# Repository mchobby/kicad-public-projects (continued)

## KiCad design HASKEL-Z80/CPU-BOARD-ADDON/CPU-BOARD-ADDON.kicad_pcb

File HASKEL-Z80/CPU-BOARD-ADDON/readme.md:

# CPU-BOARD-ADDON aka RCIO

The CPU-BOARD have been designed to deal with analogic phone system (via analog-board and interface-board).<br />In its initial state, the CPU-BOARD does not have HMI (Human Machine Interface) to allow the user to deal with the CPU-BOARD.

-1.0.jpg)

The aim of the CPU-BOARD-ADDON is to overcome this limitation with the following features:
* The CPU-BOARD-ADDON is inserted between the Z80 CPU and the CPU-BOARD, so we have access to all the buses and all the CPU signals
* **Append 8 bits outputs** (LEDs) directly controled by a IO port.<br />Requires only 2 instructions `ld a, 0xFF` followed by `out (0x1D),a`
* **Append 8 bits inputs** (button) directly accessible on IO port.<br />Requires only 2 instructions `in a,(0x1C)` followed by `ld d,a`.
* **RC2014 compatible bus** exposing all the CPU signals.<br />The RC2014 bus will be used to append additional expansion boards like [SIO-ADDON](../SIO-ADDON), [I2C-ADDON](../I2C-ADDON), etc.

The additional Input/Ouput will be very handy as basic HMI interface for testing the initial ASSEMBLY on the CPU-BOARD.

Notice: The "RCIO" comes from contraction of **RC**2014 bus and additional **I/O** .

The CPU-BOARD-ADDON will take place as follow on the CPU-BOARD.

# Schematic

Schematic is also available as PDF:
* [CPU-BOARD-ADDON-1.0.pdf](docs/CPU-BOARD-ADDON-1.0.pdf) pdf
* [CPU-BOARD-ADDON-1.1.pdf](docs/CPU-BOARD-ADDON-1.1.pdf) pdf

# Testing code

They are available on the [Z80-ASM/](../Z80-ASM) folder

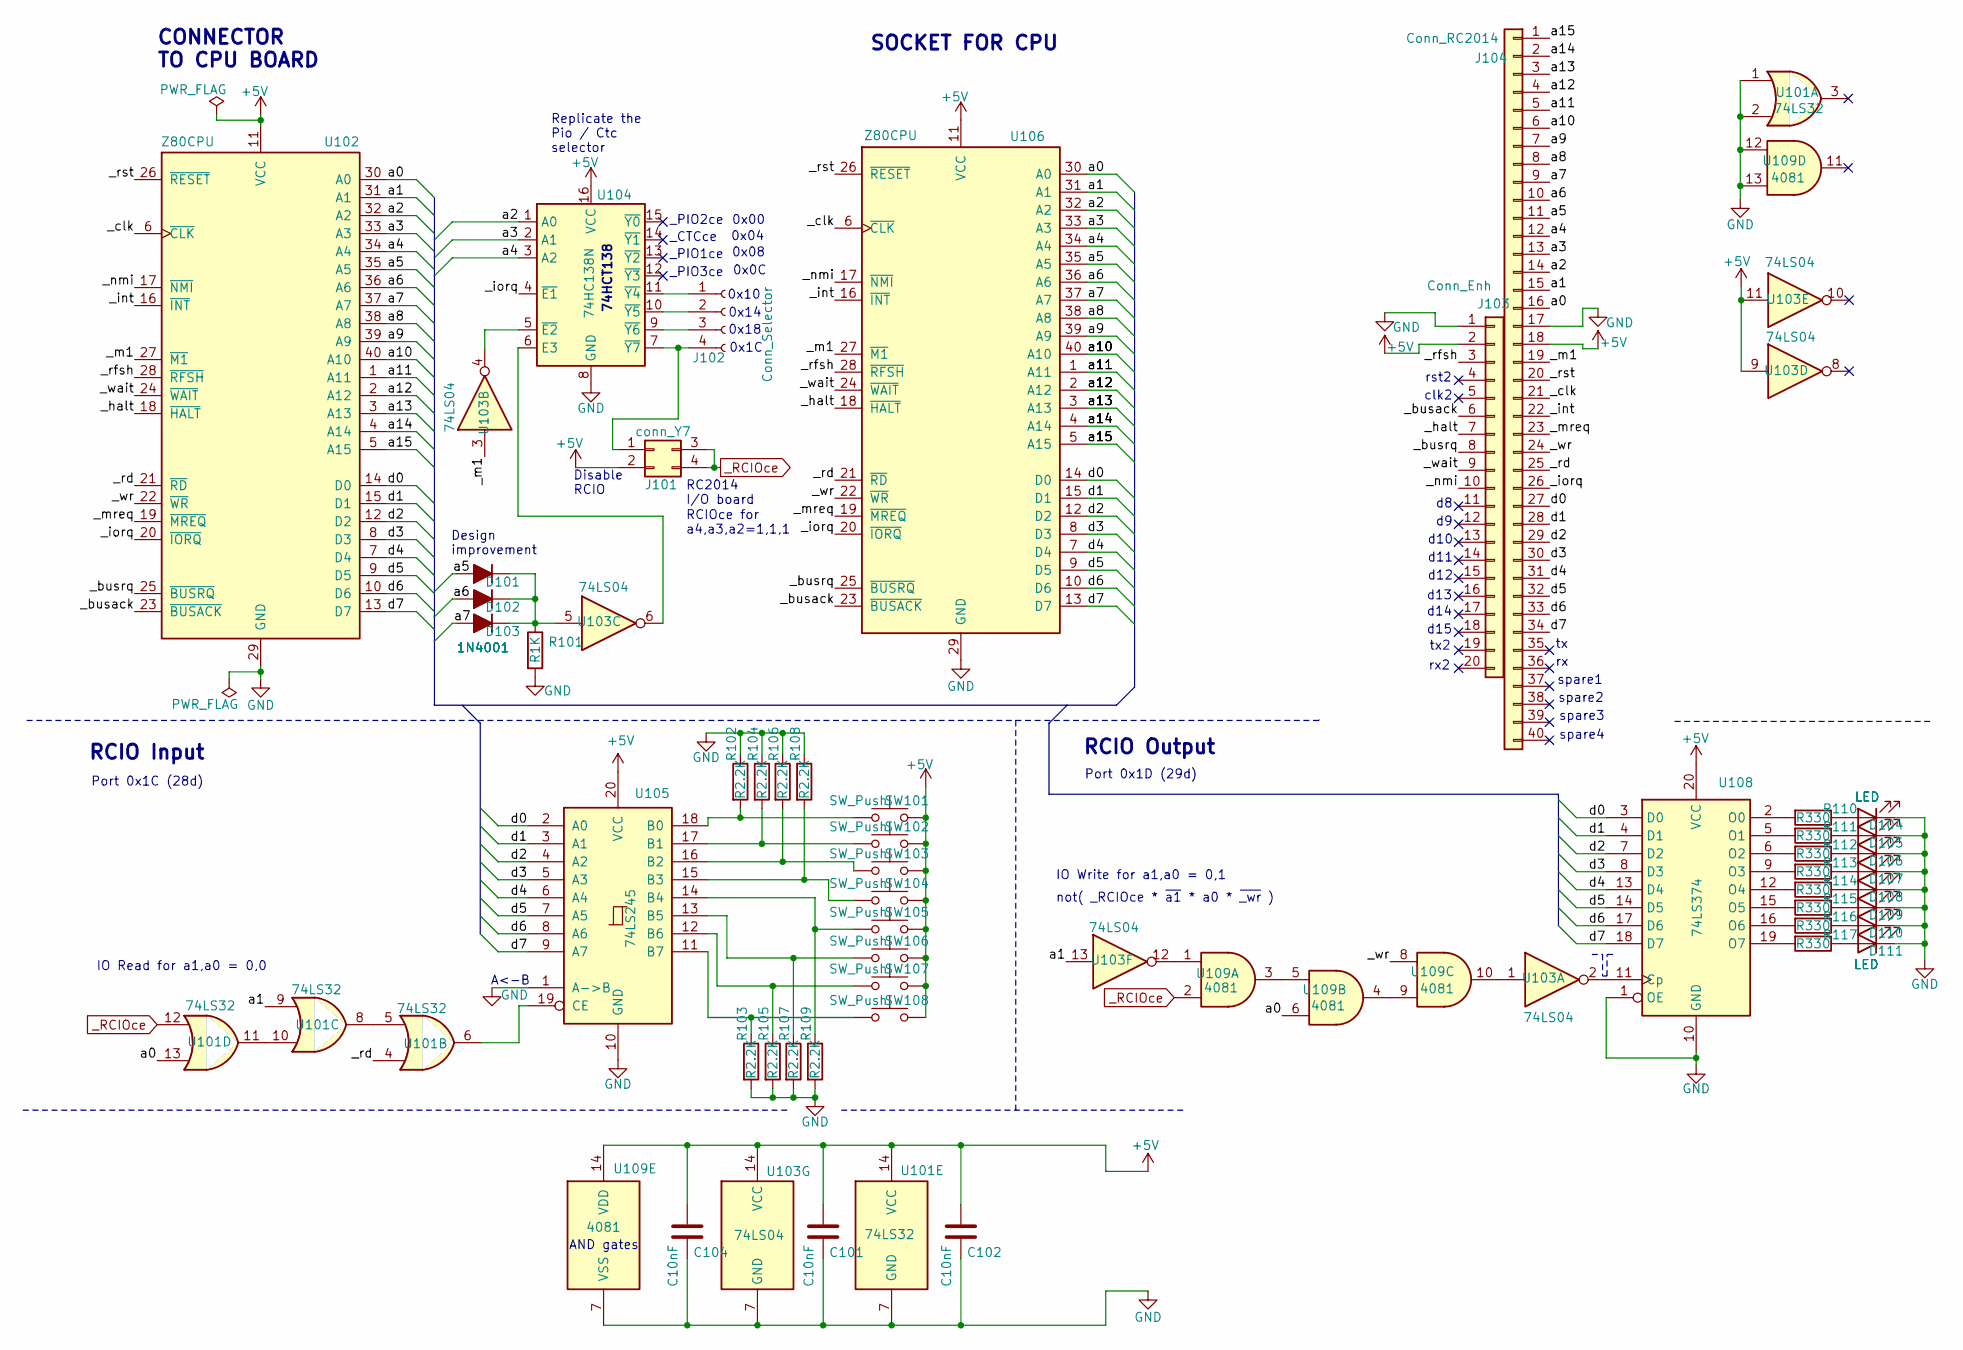
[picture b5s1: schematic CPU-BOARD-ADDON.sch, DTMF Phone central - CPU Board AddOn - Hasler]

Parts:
C101, C102, C104: C10nF; C_Disc_D3.4mm_W2.1mm_P2.50mm
D101, D102, D103: 1N4001; D_A-405_P10.16mm_Horizontal
D104, D105, D106, D107, D108, D109, D110, D111: LED; LED_D3.0mm_FlatTop
J101: conn_Y7; PinHeader_2x02_P2.54mm_Vertical
J102: Conn_Selector; PinHeader_1x04_P2.54mm_Vertical
J103: Conn_Enh; PinHeader_1x20_P2.54mm_Vertical
J104: Conn_RC2014; PinHeader_1x40_P2.54mm_Vertical
R101: R1K; R_1206_3216Metric_Pad1.30x1.75mm_HandSolder
R102, R103, R104, R105, R106, R107, R108, R109: R2.2K; R_1206_3216Metric_Pad1.30x1.75mm_HandSolder
R110, R111, R112, R113, R114, R115, R116, R117: R330; R_1206_3216Metric_Pad1.30x1.75mm_HandSolder
SW101, SW102, SW103, SW104, SW105, SW106, SW107, SW108: SW_Push; SW_Push_TL3305G_NO_4.5x4.5mm_H4.5mm
U101: 74LS32; DIP-14_W7.62mm_Socket
U102, U106: Z80CPU; DIP-40_W15.24mm_Socket_LongPads
U103: 74LS04; DIP-14_W7.62mm_Socket
U104: 74HC138N; DIP-16_W7.62mm_Socket
U105: 74LS245; DIP-20_W7.62mm_Socket
U108: 74LS374; DIP-20_W7.62mm_Socket
U109: 4081; DIP-14_W7.62mm_Socket

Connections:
+5V: C101.1, C102.1, C104.1, J101.2, J103.2, J104.18, SW101.2, SW102.2, SW103.2, SW104.2, SW105.2, SW106.2, SW107.2, SW108.2, U101.14 (VCC), U102.11 (VCC), U103.9, U103.11, U103.14 (VCC), U104.16 (VCC), U105.20 (VCC), U106.11 (VCC), U108.20 (VCC), U109.14 (VDD); also elsewhere on the board
/_busack: J103.6, U102.23 (~BUSACK~), U106.23 (~BUSACK~)
/_busrq: J103.8, U102.25 (~BUSRQ~), U106.25 (~BUSRQ~)
/_clk: J104.21, U102.6 (~CLK~), U106.6 (~CLK~)
/_halt: J103.7, U102.18 (~HALT~), U106.18 (~HALT~)
/_int: J104.22, U102.16 (~INT~), U106.16 (~INT~)
/_iorq: J104.26, U102.20 (~IORQ~), U104.4 (~E1), U106.20 (~IORQ~)
/_m1: J104.19, U102.27 (~M1~), U103.3, U106.27 (~M1~)
/_mreq: J104.23, U102.19 (~MREQ~), U106.19 (~MREQ~)
/_nmi: J103.10, U102.17 (~NMI~), U106.17 (~NMI~)
/_rd: J104.25, U101.4, U102.21 (~RD~), U106.21 (~RD~)
/_rfsh: J103.3, U102.28 (~RFSH~), U106.28 (~RFSH~)
/_rst: J104.20, U102.26 (~RESET~), U106.26 (~RESET~)
/_wait: J103.9, U102.24 (~WAIT~), U106.24 (~WAIT~)
/_wr: J104.24, U102.22 (~WR~), U106.22 (~WR~), U109.8
/a0: J104.16, U101.13, U102.30 (A0), U106.30 (A0), U109.6
/a1: J104.15, U101.9, U102.31 (A1), U103.13, U106.31 (A1)
/a2: J104.14, U102.32 (A2), U104.1 (A0), U106.32 (A2)
/a3: J104.13, U102.33 (A3), U104.2 (A1), U106.33 (A3)
/a4: J104.12, U102.34 (A4), U104.3 (A2), U106.34 (A4)
/a5: D101.2 (A), J104.11, U102.35 (A5), U106.35 (A5)
/a6: D102.2 (A), J104.10, U102.36 (A6), U106.36 (A6)
/a7: D103.2 (A), J104.9, U102.37 (A7), U106.37 (A7)
/a8: J104.8, U102.38 (A8), U106.38 (A8)
/a9: J104.7, U102.39 (A9), U106.39 (A9)
/a10: J104.6, U102.40 (A10), U106.40 (A10)
/a11: J104.5, U102.1 (A11), U106.1 (A11)
/a12: J104.4, U102.2 (A12), U106.2 (A12)
/a13: J104.3, U102.3 (A13), U106.3 (A13)
/a14: J104.2, U102.4 (A14), U106.4 (A14)
/a15: J104.1, U102.5 (A15), U106.5 (A15)
/d0: J104.27, U102.14 (D0), U105.2 (A0), U106.14 (D0), U108.3 (D0)
/d1: J104.28, U102.15 (D1), U105.3 (A1), U106.15 (D1), U108.4 (D1)
/d2: J104.29, U102.12 (D2), U105.4 (A2), U106.12 (D2), U108.7 (D2)
/d3: J104.30, U102.8 (D3), U105.5 (A3), U106.8 (D3), U108.8 (D3)
/d4: J104.31, U102.7 (D4), U105.6 (A4), U106.7 (D4), U108.13 (D4)
/d5: J104.32, U102.9 (D5), U105.7 (A5), U106.9 (D5), U108.14 (D5)
/d6: J104.33, U102.10 (D6), U105.8 (A6), U106.10 (D6), U108.17 (D6)
/d7: J104.34, U102.13 (D7), U105.9 (A7), U106.13 (D7), U108.18 (D7)
GND: C101.2, C102.2, C104.2, D104.1 (K), D105.1 (K), D106.1 (K), D107.1 (K), D108.1 (K), D109.1 (K), D110.1 (K), D111.1 (K), J103.1, J104.17, R101.2, R102.1, R103.2, R104.1, R105.2, R106.1, R107.2, R108.1, R109.2, U101.1, U101.2, U101.7 (GND), U102.29 (GND), U103.7 (GND), U104.8 (GND), U105.1 (A->B), U105.10 (GND), U106.29 (GND), U108.1 (OE), U108.10 (GND), U109.7 (VSS), U109.12, U109.13; also elsewhere on the board
unnamed: D101.1 (K), D102.1 (K), D103.1 (K), R101.1, U103.5
unnamed: D104.2 (A), R110.1
unnamed: D105.2 (A), R111.1
unnamed: D106.2 (A), R112.1
unnamed: D107.2 (A), R113.1
unnamed: D108.2 (A), R114.1
unnamed: D109.2 (A), R115.1
unnamed: D110.2 (A), R116.1
unnamed: D111.2 (A), R117.1
unnamed: J101.1, J102.4, U104.7 (~Y7)
unnamed: J102.1, U104.11 (~Y4)
unnamed: J102.2, U104.10 (~Y5)
unnamed: J102.3, U104.9 (~Y6)
unnamed: R102.2, SW101.1, U105.18 (B0)
unnamed: R103.1, SW108.1, U105.11 (B7)
unnamed: R104.2, SW102.1, U105.17 (B1)
unnamed: R105.1, SW107.1, U105.12 (B6)
unnamed: R106.2, SW103.1, U105.16 (B2)
unnamed: R107.1, SW106.1, U105.13 (B5)
unnamed: R108.2, SW104.1, U105.15 (B3)
unnamed: R109.1, SW105.1, U105.14 (B4)
unnamed: R110.2, U108.2 (O0)
unnamed: R111.2, U108.5 (O1)
unnamed: R112.2, U108.6 (O2)
unnamed: R113.2, U108.9 (O3)
unnamed: R114.2, U108.12 (O4)
unnamed: R115.2, U108.15 (O5)
unnamed: R116.2, U108.16 (O6)
unnamed: R117.2, U108.19 (O7)
unnamed: U101.5, U101.8
unnamed: U101.6, U105.19 (CE)
unnamed: U101.10, U101.11
unnamed: U103.1, U109.10
unnamed: U103.2, U108.11 (Cp)
unnamed: U103.4, U104.5 (~E2)
unnamed: U103.6, U104.6 (E3)
unnamed: U103.12, U109.1
unnamed: U109.3, U109.5
unnamed: U109.4, U109.9
_RCIOce: J101.3, J101.4, U101.12, U109.2

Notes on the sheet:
CONNECTOR TO CPU BOARD
SOCKET FOR CPU
_PIO2ce
_CTCce
_PIO1ce
_PIO3ce
RC2014 I/O board
Replicate the Pio / Ctc selector
A<-B
IO Read for a1,a0 = 0,0
RCIOce for a4,a3,a2=1,1,1
RCIO Input
Port 0x1C (28d)
RCIO Output
Port 0x1D (29d)
Disable RCIO
IO Write for a1,a0 = 0,1
Design improvement
d10
d11
d12
d13
d14
d15
tx2
rx2
spare1
spare2
spare3
spare4
rst2
clk2
0x00
0x04
0x08
0x0C
0x10
0x14
0x18
0x1C

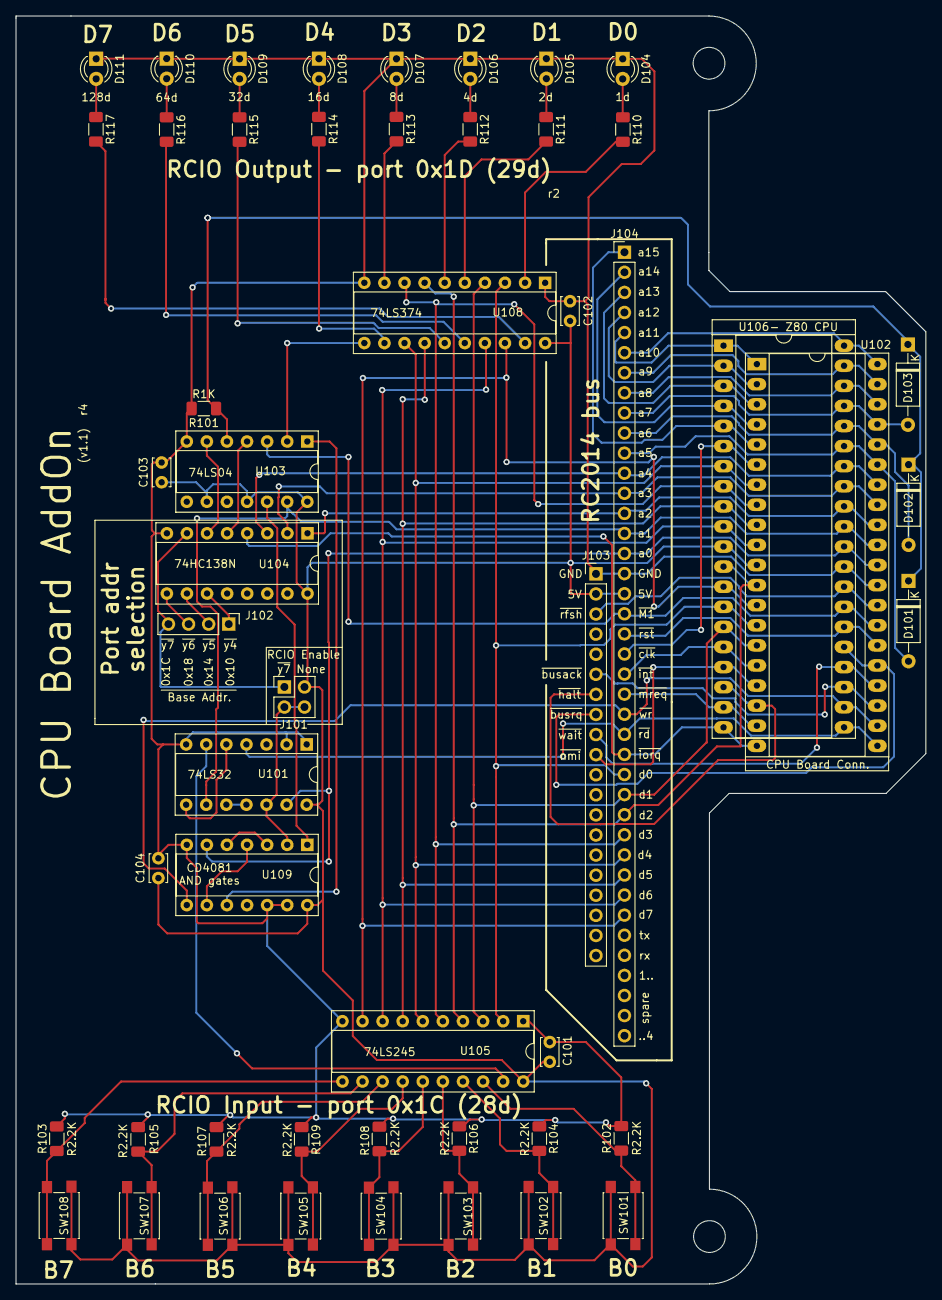
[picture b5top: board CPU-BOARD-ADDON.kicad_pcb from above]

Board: 2 copper layers, 115.0 x 160.3 mm, 52 parts (0 on the bottom side), 80 nets.

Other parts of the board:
C103: C10nF; C_Disc_D3.4mm_W2.1mm_P2.50mm

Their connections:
+5V: C103.1; also elsewhere on the board
GND: C103.2; also elsewhere on the board

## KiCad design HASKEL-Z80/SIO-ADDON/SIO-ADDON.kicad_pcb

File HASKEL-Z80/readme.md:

# Haskel Z80 based DTMF phone central

I wanted to explore the Z80 programming in assembly and C but have no hardware available.

After [some experiment with the great RC2014 kit](https://arduino103.blogspot.com/search/label/RC2014) able to run CP/M and using in-RAM assembly, I decided to go for a new projet.

This time I wanted to salvage a Z80 board, learn more about hardware design and hack it to expand its capabilities.

This is where I met this DTMF (tone) phone central based on Z80.

This central is composed of CPU-BOARD, Analog board and Interface board (to phone lines). The board of interest is the CPU-BOARD.

# Haskel Z80 Hack History

Here below the CPU-Board with an RCIO Input/Output expansion board plugged directly onto the Z80 CPU.

Features of the CPU-BOARD:
* 1x Z80 CPU @ 2 MHz
* 3x Z80 PIO - As many as 48 IOs
* 1x Z80 CTC - Timer / Counter
* 1x 2Ko RAM
* 3x 32Ko ROM
* 1x Watchdog circuitery (IC15 removed to disable)
* 1x DTMF generator
* 1x 46 pins PIO connector (P1)
* 1x 16 pins PWR connector (P2)
 * 5 Volts
 * +12 Volts (not used on CPU-BOARD)
 * -12 Volts (not used on CPU-BOARD)

Here an history of the projet developemnt

| **Date** | **Folder** | **Description** |
|----------|------------|-----------------|
| Jun 2023 | [CPU-BOARD/](CPU-BOARD) |  Reverse engineered of the main CPU board with Kicad schematic, memory addressing, hacking (to add expansion boards), etc |
| Jun 2023 | [EPROM-27512-GLS27SF512/](EPROM-27512-GLS27SF512) | Replacing the UVProm by an EEPROM (GLS27SF512 erasable Flash) |
| Jun 2023 | [PROGRAMMER-GLS27SF512/](PROGRAMMER-GLS27SF512) | Attempt to create a MicroPython programmer for GLS27SF512 Flash (**Doesn't works on writing!**, I now use a XGecu Pro)
| Aug 2023 | [EPROM-27512-GLS27SF512-v2/](EPROM-27512-GLS27SF512-v2) | Also a replacement of the UVProm but using a socket for the PLCC Flash component |
| oct 2023 | [CPU-BOARD-ADDON/](CPU-BOARD-ADDON) | This companion board is also named "RCIO" because it brings a RC2014 like expansion port, 8x I/O input (button) and 8x output (LED). This board will plug directly on the Z80 cpu and allow additionnal expansion to be plugged on the CPU board.|
| Sep 2023 | [Z80-ASM/](Z80-ASM) | Programming and learning Z80 step by step. ASM libraries and examples. |
| Nov 2023 | [Z80-ASM/test-lcd/](Z80-ASM/test-lcd) | Driving a 20x4 LCD display from the CPU-BOARD PIO. |
| --- | SIO-ADDON/ | **Under construction** Serial Interface for the CPU-BOARD. |
| --- | I2C-ADDON/ | **Under construction** I2C interface for the CPU-BOARD.    |
| --- | ANALOG-BOARD/ | **Under construction** Reverse engineering of the Analog board (and its usage with the CPU board).    |

# More information

If you want to discover more about this retro-ingeneering story, just have a look to the following links:
* [Retro ingénierie d'une carte Z80](https://arduino103.blogspot.com/search/label/Z80-ASM) on the MCHobby's blog
* [Discussion thread of the project](https://forum.system-cfg.com/viewtopic.php?f=18&t=14526) on System.cfg forum

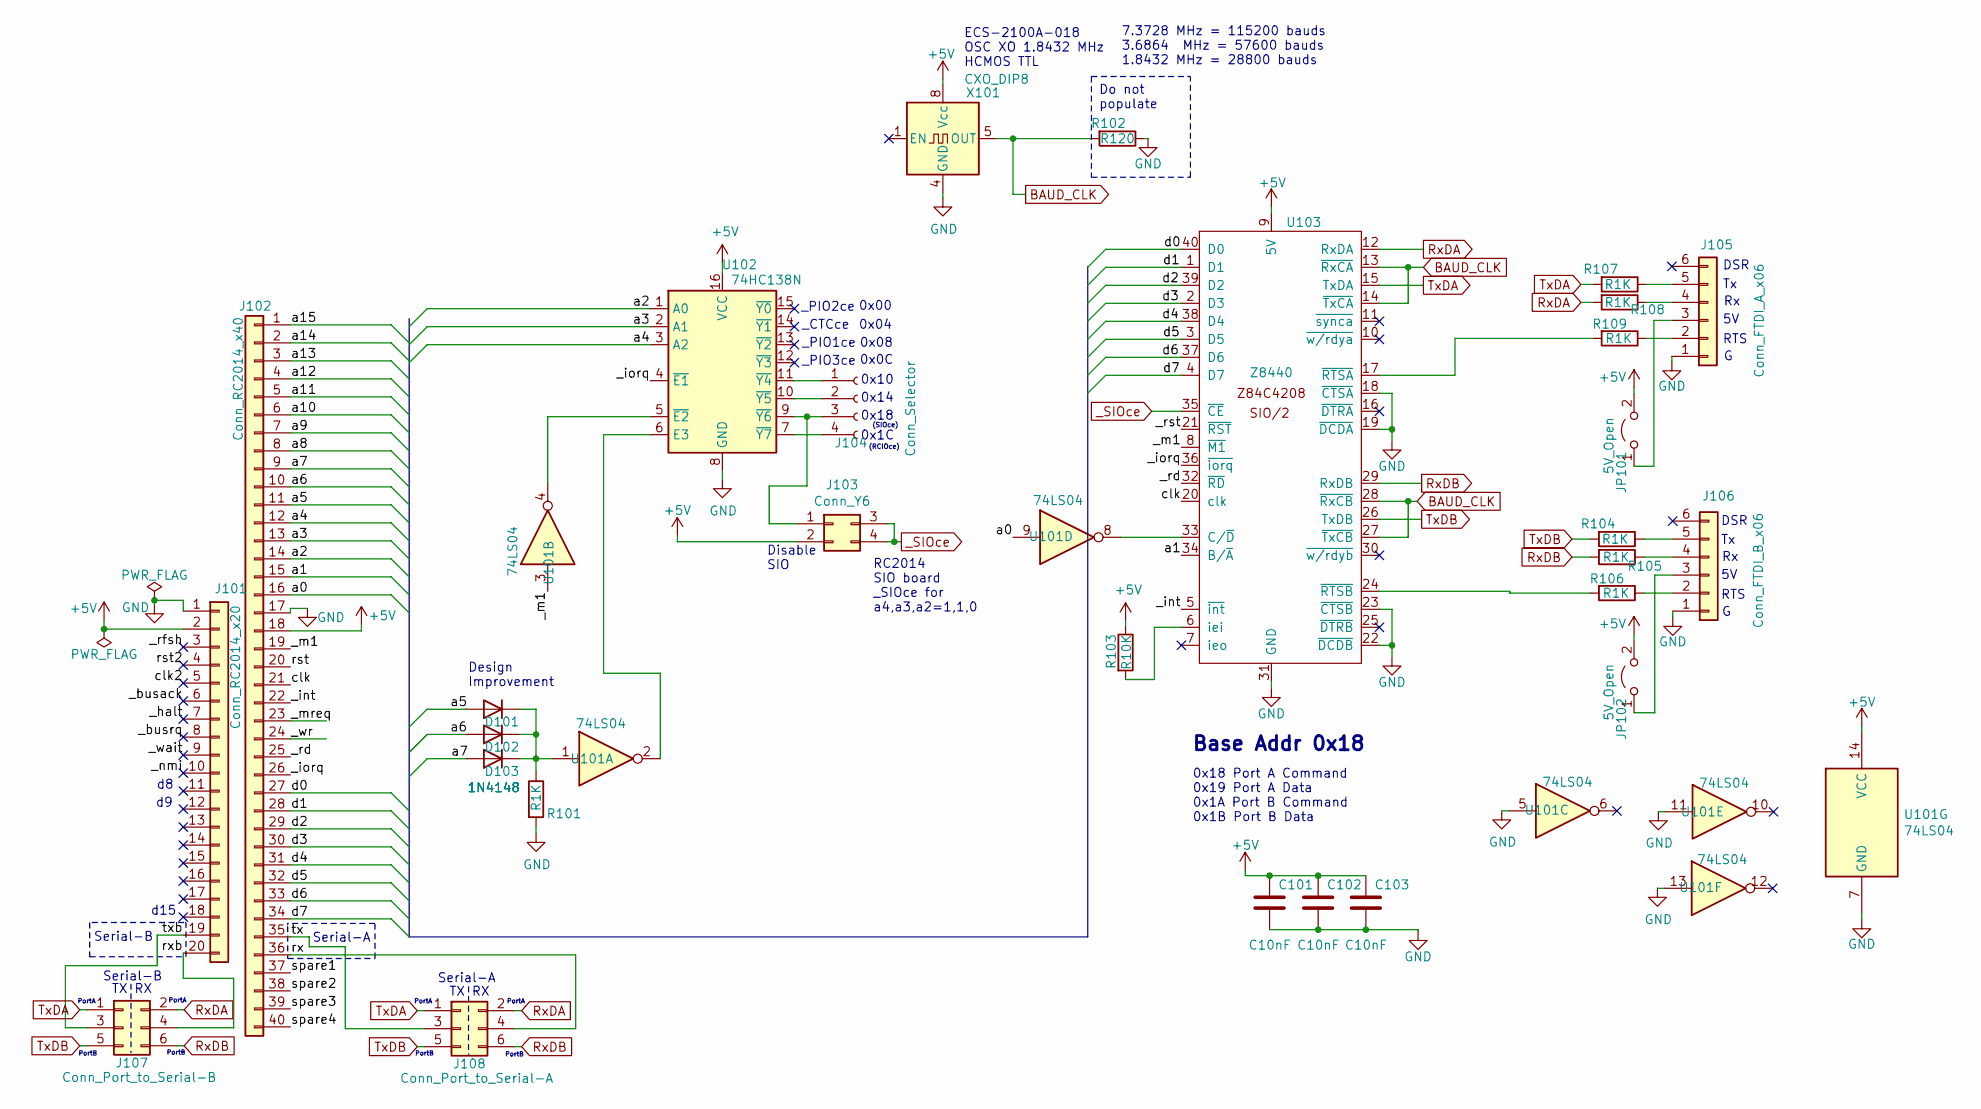
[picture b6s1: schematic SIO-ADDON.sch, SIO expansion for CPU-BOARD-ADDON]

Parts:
C101, C102, C103: C10nF; C_Disc_D4.7mm_W2.5mm_P5.00mm
D101, D102, D103: 1N4148; D_DO-35_SOD27_P7.62mm_Horizontal
J101: Conn_RC2014_x20; PinHeader_1x20_P2.54mm_Vertical
J102: Conn_RC2014_x40; PinHeader_1x40_P2.54mm_Vertical
J103: Conn_Y6; PinHeader_2x02_P2.54mm_Vertical
J104: Conn_Selector; PinHeader_1x04_P2.54mm_Vertical
J105: Conn_FTDI_A_x06; PinHeader_1x06_P2.54mm_Horizontal
J106: Conn_FTDI_B_x06; PinHeader_1x06_P2.54mm_Horizontal
J107: Conn_Port_to_Serial-B; PinHeader_2x03_P2.54mm_Vertical
J108: Conn_Port_to_Serial-A; PinHeader_2x03_P2.54mm_Vertical
JP101, JP102: 5V_Open; PinHeader_1x02_P2.54mm_Vertical
R101, R104, R105, R106, R107, R108, R109: R1K; R_Axial_DIN0207_L6.3mm_D2.5mm_P10.16mm_Horizontal
R102: R120; R_Axial_DIN0207_L6.3mm_D2.5mm_P10.16mm_Horizontal
R103: R10K; R_Axial_DIN0207_L6.3mm_D2.5mm_P10.16mm_Horizontal
U101: 74LS04; DIP-14_W7.62mm_LongPads
U102: 74HC138N; DIP-16_W7.62mm_LongPads
U103: Z8440; DIP-40_W15.24mm
X101: CXO_DIP8; Oscillator_DIP-8

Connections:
+5V: C101.1, C102.1, C103.1, J101.2, J102.18, J103.2, JP101.2 (B), JP102.2 (B), R103.1, U101.14 (VCC), U102.16 (VCC), U103.9 (5V), X101.8 (Vcc)
/_busack: J101.6
/_busrq: J101.8
/_halt: J101.7
/_int: J102.22, U103.5 (~int)
/_iorq: J102.26, U102.4 (~E1), U103.36 (~iorq)
/_m1: J102.19, U101.3, U103.8 (~M1)
/_mreq: J102.23
/_nmi: J101.10
/_rd: J102.25, U103.32 (~RD)
/_rfsh: J101.3
/_rst: U103.21 (~RST)
/_wait: J101.9
/_wr: J102.24
/a0: J102.16, U101.9
/a1: J102.15, U103.34 (B/~A)
/a2: J102.14, U102.1 (A0)
/a3: J102.13, U102.2 (A1)
/a4: J102.12, U102.3 (A2)
/a5: D101.2 (A), J102.11
/a6: D102.2 (A), J102.10
/a7: D103.2 (A), J102.9
/a8: J102.8
/a9: J102.7
/a10: J102.6
/a11: J102.5
/a12: J102.4
/a13: J102.3
/a14: J102.2
/a15: J102.1
/clk: J102.21, U103.20 (clk)
/clk2: J101.5
/d0: J102.27, U103.40 (D0)
/d1: J102.28, U103.1 (D1)
/d2: J102.29, U103.39 (D2)
/d3: J102.30, U103.2 (D3)
/d4: J102.31, U103.38 (D4)
/d5: J102.32, U103.3 (D5)
/d6: J102.33, U103.37 (D6)
/d7: J102.34, U103.4 (D7)
/rst: J102.20
/rst2: J101.4
/rx: J102.36, J108.4
/rxb: J101.20, J107.4
/spare1: J102.37
/spare2: J102.38
/spare3: J102.39
/spare4: J102.40
/tx: J102.35, J108.3
/txb: J101.19, J107.3
BAUD_CLK: R102.2, U103.13 (~RxCA), U103.14 (~TxCA), U103.27 (~TxCB), U103.28 (~RxCB), X101.5 (OUT)
GND: C101.2, C102.2, C103.2, J101.1, J102.17, J105.1, J106.1, R101.2, R102.1, U101.5, U101.7 (GND), U101.11, U101.13, U102.8 (GND), U103.18 (~CTSA), U103.19 (~DCDA), U103.22 (~DCDB), U103.23 (~CTSB), U103.31 (GND), X101.4 (GND)
unnamed: D101.1 (K), D102.1 (K), D103.1 (K), R101.1, U101.1
unnamed: J103.1, J104.3, U102.9 (~Y6)
unnamed: J104.1, U102.11 (~Y4)
unnamed: J104.2, U102.10 (~Y5)
unnamed: J104.4, U102.7 (~Y7)
unnamed: J105.2, R109.1
unnamed: J105.3, JP101.1 (A)
unnamed: J105.4, R108.1
unnamed: J105.5, R107.1
unnamed: J106.2, R106.1
unnamed: J106.3, JP102.1 (A)
unnamed: J106.4, R105.1
unnamed: J106.5, R104.1
unnamed: R103.2, U103.6 (iei)
unnamed: R106.2, U103.24 (~RTSB)
unnamed: R109.2, U103.17 (~RTSA)
unnamed: U101.2, U102.6 (E3)
unnamed: U101.4, U102.5 (~E2)
unnamed: U101.8, U103.33 (C/~D)
RxDA: J107.2, J108.2, R108.2, U103.12 (RxDA)
RxDB: J107.6, J108.6, R105.2, U103.29 (RxDB)
TxDA: J107.1, J108.1, R107.2, U103.15 (TxDA)
TxDB: J107.5, J108.5, R104.2, U103.26 (TxDB)
_SIOce: J103.3, J103.4, U103.35 (~CE)

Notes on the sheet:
ECS-2100A-018 OSC XO 1.8432 MHz HCMOS TTL
Do not populate
d15
_PIO2ce
_CTCce
_PIO1ce
_PIO3ce
0x00
0x04
0x08
0x0C
0x10
0x14
0x18
0x1C
(RCIOce)
(SIOce)
Disable SIO
Design Improvement
RC2014 SIO board _SIOce for a4,a3,a2=1,1,0
Base Addr 0x18
7.3728 MHz = 115200 bauds 3.6864 MHz = 57600 bauds 1.8432 MHz = 28800 bauds
RTS
DSR
0x18 Port A Command 0x19 Port A Data 0x1A Port B Command 0x1B Port B Data
Serial-A
Serial-B
PortA
PortB

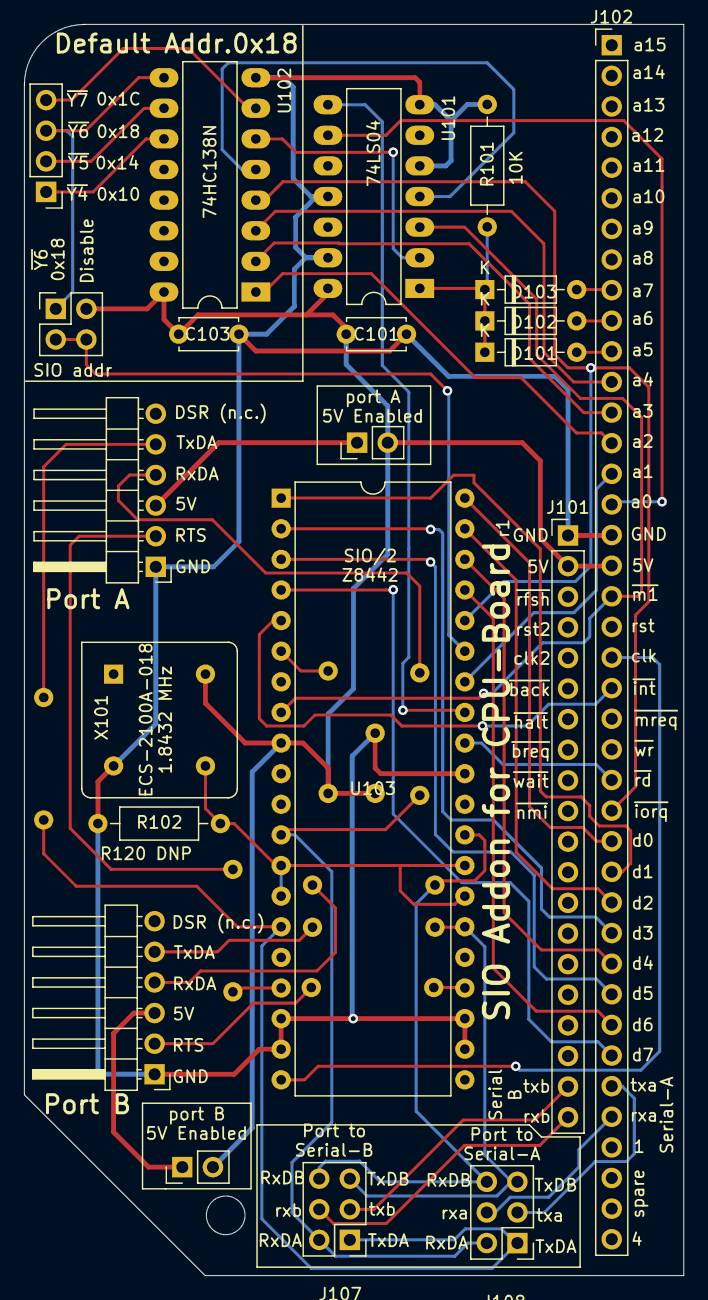
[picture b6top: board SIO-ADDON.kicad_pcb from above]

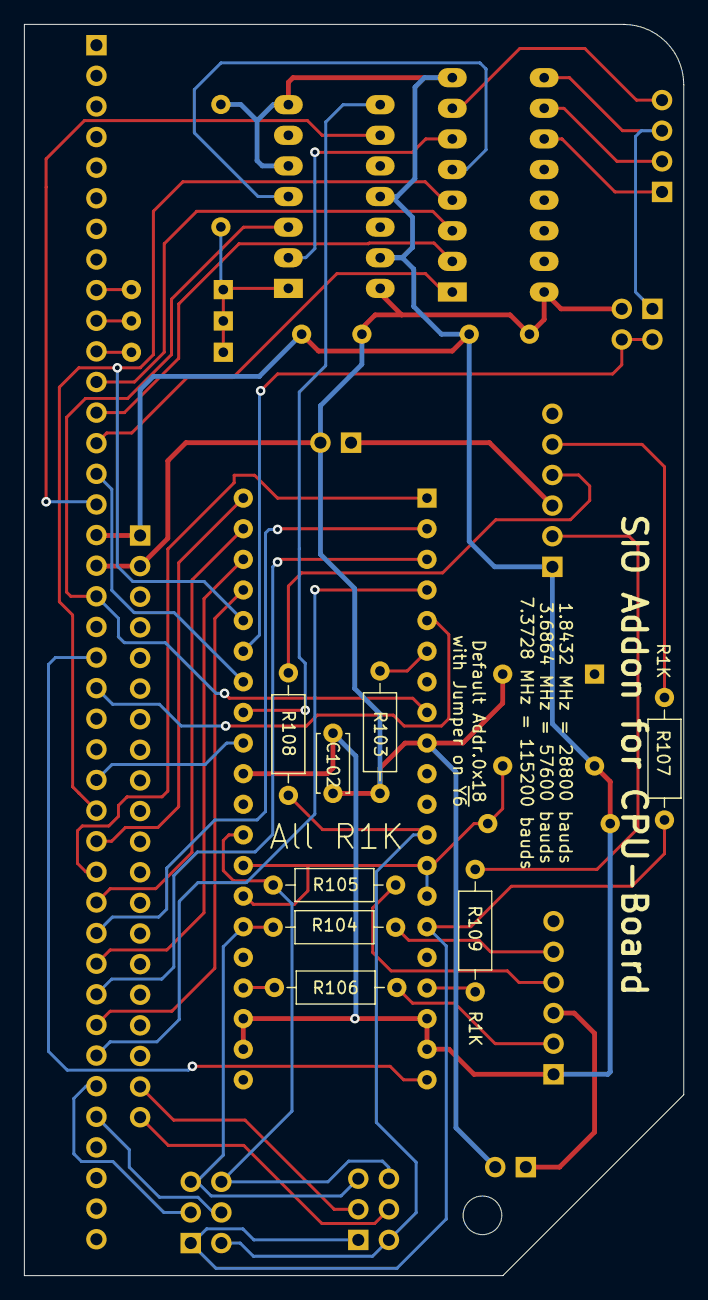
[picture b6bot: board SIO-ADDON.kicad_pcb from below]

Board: 2 copper layers, 54.7 x 103.8 mm, 29 parts (8 on the bottom side), 52 nets.

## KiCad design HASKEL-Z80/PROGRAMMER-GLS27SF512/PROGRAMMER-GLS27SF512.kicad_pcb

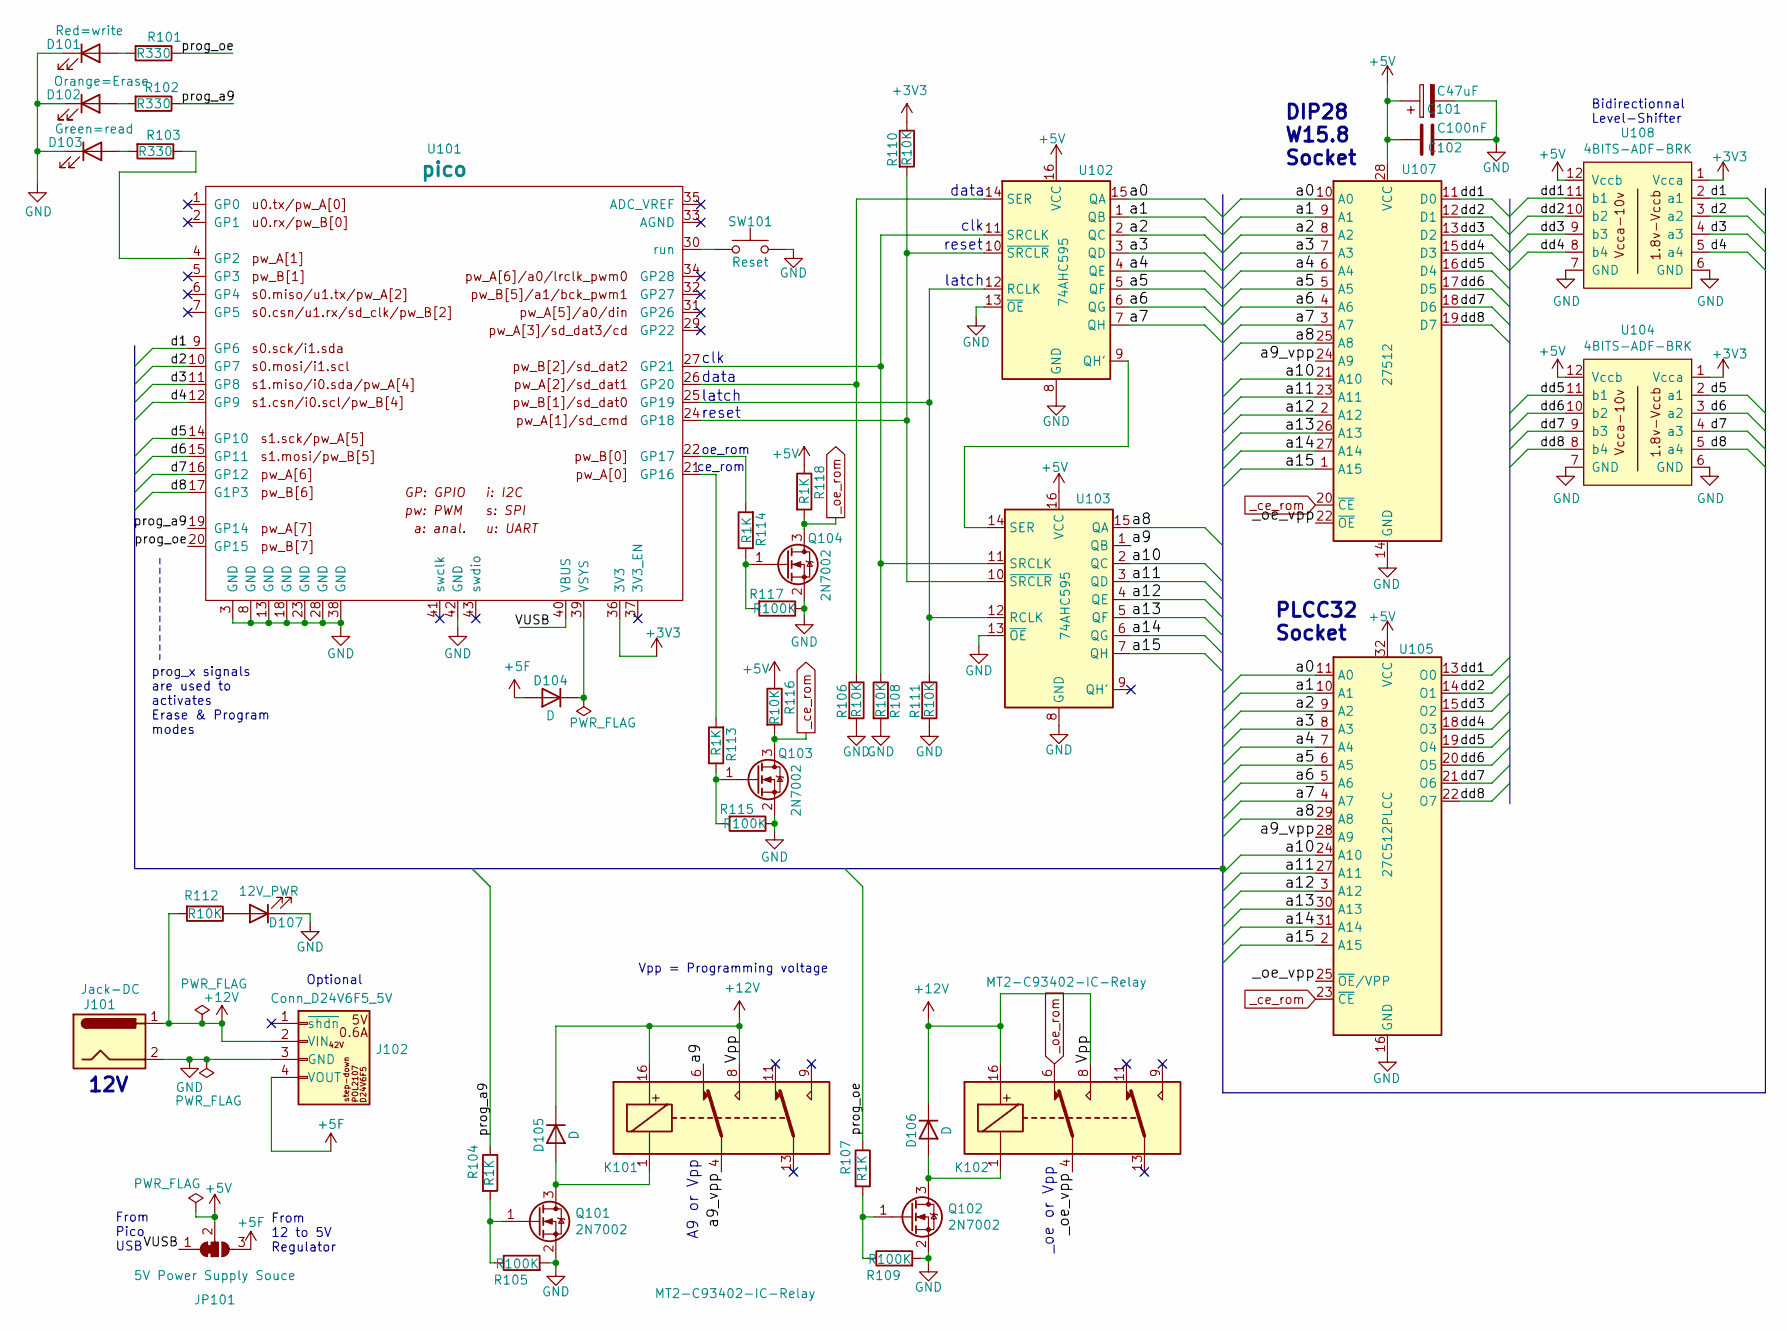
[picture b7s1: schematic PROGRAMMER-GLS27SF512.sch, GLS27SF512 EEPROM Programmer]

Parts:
C101: C47uF; CP_Radial_D6.3mm_P2.50mm
C102: C100nF; C_Disc_D7.5mm_W2.5mm_P5.00mm
D101: Red=write; LED_1206_3216Metric_Pad1.42x1.75mm_HandSolder
D102: Orange=Erase; LED_1206_3216Metric_Pad1.42x1.75mm_HandSolder
D103: Green=read; LED_1206_3216Metric_Pad1.42x1.75mm_HandSolder
D104: D; D_1206_3216Metric_Pad1.42x1.75mm_HandSolder
D105, D106: D; D_A-405_P7.62mm_Horizontal
D107: 12V_PWR; LED_1206_3216Metric_Pad1.42x1.75mm_HandSolder
J101: Jack-DC; BarrelJack_Wuerth_6941xx301002
J102: Conn_D24V6F5_5V; PinHeader_1x04_P2.54mm_Vertical
JP101: 5V Power Supply Souce; SolderJumper-3_P1.3mm_Bridged12_Pad1.0x1.5mm
K101, K102: MT2-C93402-IC-Relay; DIP-16_W7.62mm_LongPads
Q101, Q102, Q103, Q104: 2N7002; SOT-23
R101, R102, R103: R330; R_1206_3216Metric_Pad1.30x1.75mm_HandSolder
R104, R107, R113, R114, R118: R1K; R_1206_3216Metric_Pad1.30x1.75mm_HandSolder
R105, R109, R115, R117: R100K; R_1206_3216Metric_Pad1.30x1.75mm_HandSolder
R106, R108, R110, R111, R112, R116: R10K; R_1206_3216Metric_Pad1.30x1.75mm_HandSolder
SW101: Reset; SW_Push_TL3305G_NO_4.5x4.5mm_H4.5mm
U101: pico; PICO
U102, U103: 74AHC595; DIP-16_W7.62mm_LongPads
U104, U108: 4BITS-ADF-BRK; ADF757-12-W10.16
U105: 27C512PLCC; PLCC-32_THT-Socket
U107: 27512; DIP-28_W15.24mm

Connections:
+3V3: R110.1, U101.36 (3V3), U104.1 (Vcca), U108.1 (Vcca)
+5F: D104.2 (A), J102.4 (VOUT), JP101.3 (B)
+5V: C101.1, C102.2, JP101.2 (C), R116.1, R118.1, U102.16 (VCC), U103.16 (VCC), U104.12 (Vccb), U105.32 (VCC), U107.28 (VCC), U108.12 (Vccb)
+12V: D105.1 (K), D106.1 (K), J101.1, J102.2 (VIN), K101.8, K101.16, K102.8, K102.16, R112.2
/VUSB: JP101.1 (A), U101.40 (VBUS)
/_oe_vpp: K102.4, U105.25 (~OE~/VPP), U107.22 (~OE)
/a0: U102.15 (QA), U105.11 (A0), U107.10 (A0)
/a1: U102.1 (QB), U105.10 (A1), U107.9 (A1)
/a2: U102.2 (QC), U105.9 (A2), U107.8 (A2)
/a3: U102.3 (QD), U105.8 (A3), U107.7 (A3)
/a4: U102.4 (QE), U105.7 (A4), U107.6 (A4)
/a5: U102.5 (QF), U105.6 (A5), U107.5 (A5)
/a6: U102.6 (QG), U105.5 (A6), U107.4 (A6)
/a7: U102.7 (QH), U105.4 (A7), U107.3 (A7)
/a8: U103.15 (QA), U105.29 (A8), U107.25 (A8)
/a9: K101.6, U103.1 (QB)
/a9_vpp: K101.4, U105.28 (A9), U107.24 (A9)
/a10: U103.2 (QC), U105.24 (A10), U107.21 (A10)
/a11: U103.3 (QD), U105.27 (A11), U107.23 (A11)
/a12: U103.4 (QE), U105.3 (A12), U107.2 (A12)
/a13: U103.5 (QF), U105.30 (A13), U107.26 (A13)
/a14: U103.6 (QG), U105.31 (A14), U107.27 (A14)
/a15: U103.7 (QH), U105.2 (A15), U107.1 (A15)
/d1: U101.9 (GP6), U108.2 (a1)
/d2: U101.10 (GP7), U108.3 (a2)
/d3: U101.11 (GP8), U108.4 (a3)
/d4: U101.12 (GP9), U108.5 (a4)
/d5: U101.14 (GP10), U104.2 (a1)
/d6: U101.15 (GP11), U104.3 (a2)
/d7: U101.16 (GP12), U104.4 (a3)
/d8: U101.17 (G1P3), U104.5 (a4)
/dd1: U105.13 (O0), U107.11 (D0), U108.11 (b1)
/dd2: U105.14 (O1), U107.12 (D1), U108.10 (b2)
/dd3: U105.15 (O2), U107.13 (D2), U108.9 (b3)
/dd4: U105.18 (O3), U107.15 (D3), U108.8 (b4)
/dd5: U104.11 (b1), U105.19 (O4), U107.16 (D4)
/dd6: U104.10 (b2), U105.20 (O5), U107.17 (D5)
/dd7: U104.9 (b3), U105.21 (O6), U107.18 (D6)
/dd8: U104.8 (b4), U105.22 (O7), U107.19 (D7)
/prog_a9: R102.1, R104.1, U101.19 (GP14)
/prog_oe: R101.1, R107.1, U101.20 (GP15)
GND: C101.2, C102.1, D101.1 (K), D102.1 (K), D103.1 (K), D107.1 (K), J101.2, J102.3 (GND), Q101.2 (S), Q102.2 (S), Q103.2 (S), Q104.2 (S), R105.2, R106.2, R108.2, R109.2, R111.2, R115.1, R117.1, SW101.2, U101.3 (GND), U101.8 (GND), U101.13 (GND), U101.18 (GND), U101.23 (GND), U101.28 (GND), U101.38 (GND), U101.42 (GND), U102.8 (GND), U102.13 (~OE), U103.8 (GND), U103.13 (~OE), U104.6 (GND), U104.7 (GND), U105.16 (GND), U107.14 (GND), U108.6 (GND), U108.7 (GND)
unnamed: D101.2 (A), R101.2
unnamed: D102.2 (A), R102.2
unnamed: D103.2 (A), R103.2
unnamed: D104.1 (K), U101.39 (VSYS)
unnamed: D105.2 (A), K101.1, Q101.3 (D)
unnamed: D106.2 (A), K102.1, Q102.3 (D)
unnamed: D107.2 (A), R112.1
unnamed: Q101.1 (G), R104.2, R105.1
unnamed: Q102.1 (G), R107.2, R109.1
unnamed: Q103.1 (G), R113.1, R115.2
unnamed: Q104.1 (G), R114.1, R117.2
unnamed: R103.1, U101.4 (GP2)
unnamed: R106.1, U101.26 (GP20), U102.14 (SER)
unnamed: R108.1, U101.27 (GP21), U102.11 (SRCLK), U103.11 (SRCLK)
unnamed: R110.2, U101.24 (GP18), U102.10 (~SRCLR), U103.10 (~SRCLR)
unnamed: R111.1, U101.25 (GP19), U102.12 (RCLK), U103.12 (RCLK)
unnamed: R113.2, U101.21 (GP16)
unnamed: R114.2, U101.22 (GP17)
unnamed: SW101.1, U101.30 (run)
unnamed: U102.9 (QH'), U103.14 (SER)
_ce_rom: Q103.3 (D), R116.2, U105.23 (~CE), U107.20 (~CE)
_oe_rom: K102.6, Q104.3 (D), R118.2

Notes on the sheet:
12V
clk
data
reset
latch
_oe or Vpp
A9 or Vpp
Vpp = Programming voltage
Bidirectionnal Level-Shifter
DIP28 W15.8 Socket
PLCC32 Socket
prog_x signals are used to activates Erase & Program modes
oe_rom
ce_rom
Optional
From 12 to 5V Regulator
From Pico USB

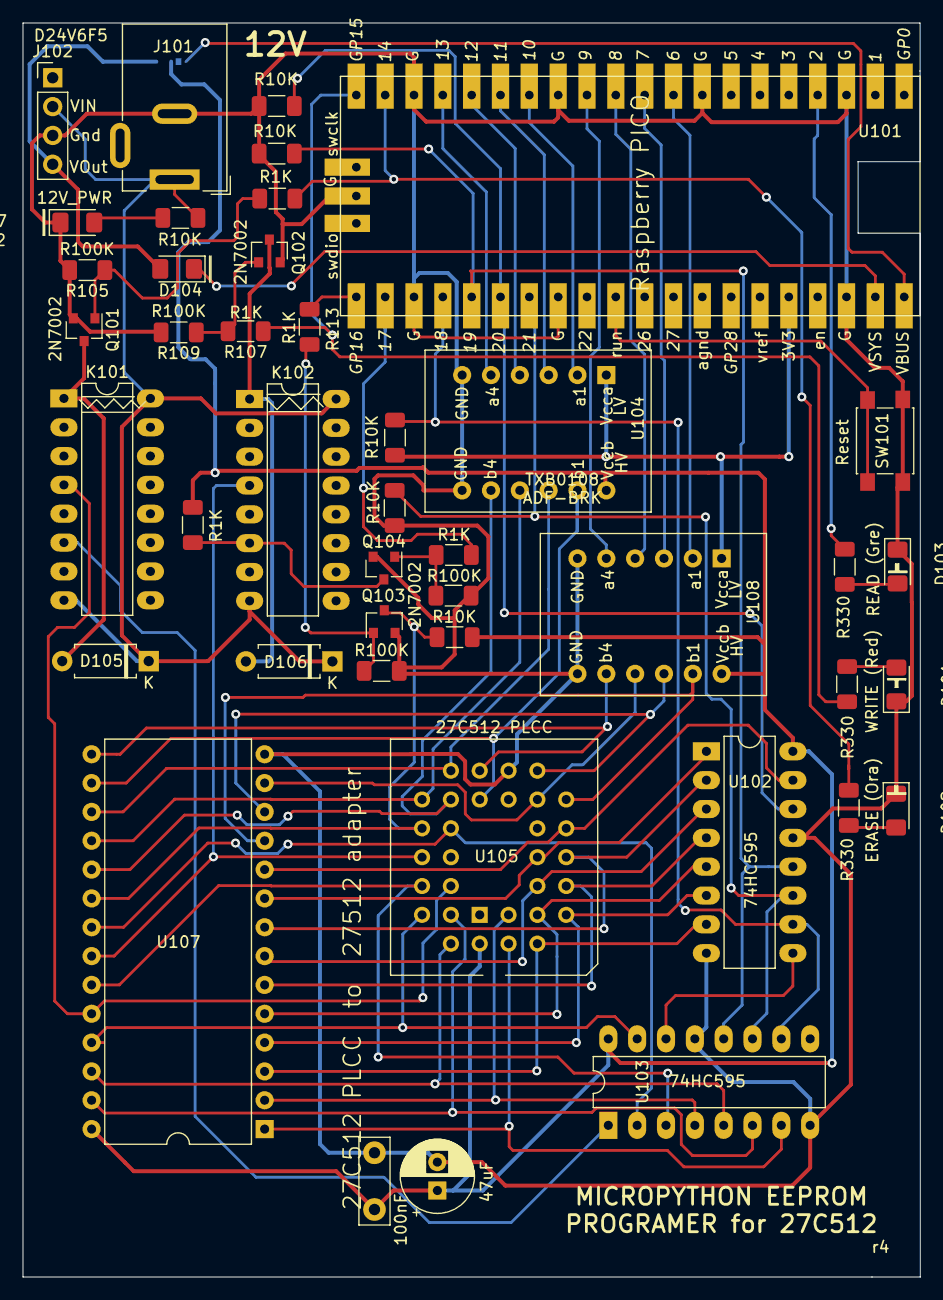
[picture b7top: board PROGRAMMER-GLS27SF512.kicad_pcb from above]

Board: 2 copper layers, 79.0 x 110.5 mm, 44 parts (1 on the bottom side), 64 nets.
